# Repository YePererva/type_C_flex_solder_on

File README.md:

# Type C upgrade kits

Status: Work in progress

Stage: Search for affordable prototyping facility

## About:

This repository contains developments on **_in-situ_** upgrade kits for older Micro/Mini USB ports with USB Type C. The idea is to have flex-PCB (or on very thin FR-4), where:

- USB Type port is located on top layer, accompanied by a pair of 5K1 resistors. 
- Mirrored footprint of a Micro (or Mini) USB port is situated at the bottom layer.
- Use of 0603 size of resistors would keep this project manually solderable

Theoretically, it allows for upgrading older devices by directly soldering of adapter over existing footprint. 

The Content Repository contains three variations of adapters:

- `micro_edge`
    
    prototype of micro USB replacement, where alignment is done on the PCB edge, as is typical for ports.

- `mini_edge`
    
    prototype of mini USB replacement, where alignment is done on the PCB edge, as is typical for ports. It is interesting to note that the mini USB port appears to be of a greater length than that of the type C port.

- `micro_pads`
    
    this prototype is a design for a micro USB replacement, in which is allinged relatively to the pads of micro USB port. This is applicable in instances where the presence of additional circuitry in close proximity to the port renders edge alignment unfeasible. It results in a longer outlet of the Type C port protruding from the PCB edge.  

## Some visuals

|   | Micro Edge | Mini Edge | Micro Pads |
| ------------- | ------------- |  ------------- |  ------------- |
| Top View  |   |   |   |
| Bottom View  |   |   |   |

## Remarks / Thoughts / Things to test

- The utilisation of tape adhesive might be necessary for the positioning.
- Thin FR-4 might provide more rigidity than FlexPCBs
- Silkscreen has multiple perimeters. THis is for manual adjusting of form where space limitation might require it.
- For panelization of multiple designs, I found [this](https://github.com/buganini/Kikakuka) tool useful.

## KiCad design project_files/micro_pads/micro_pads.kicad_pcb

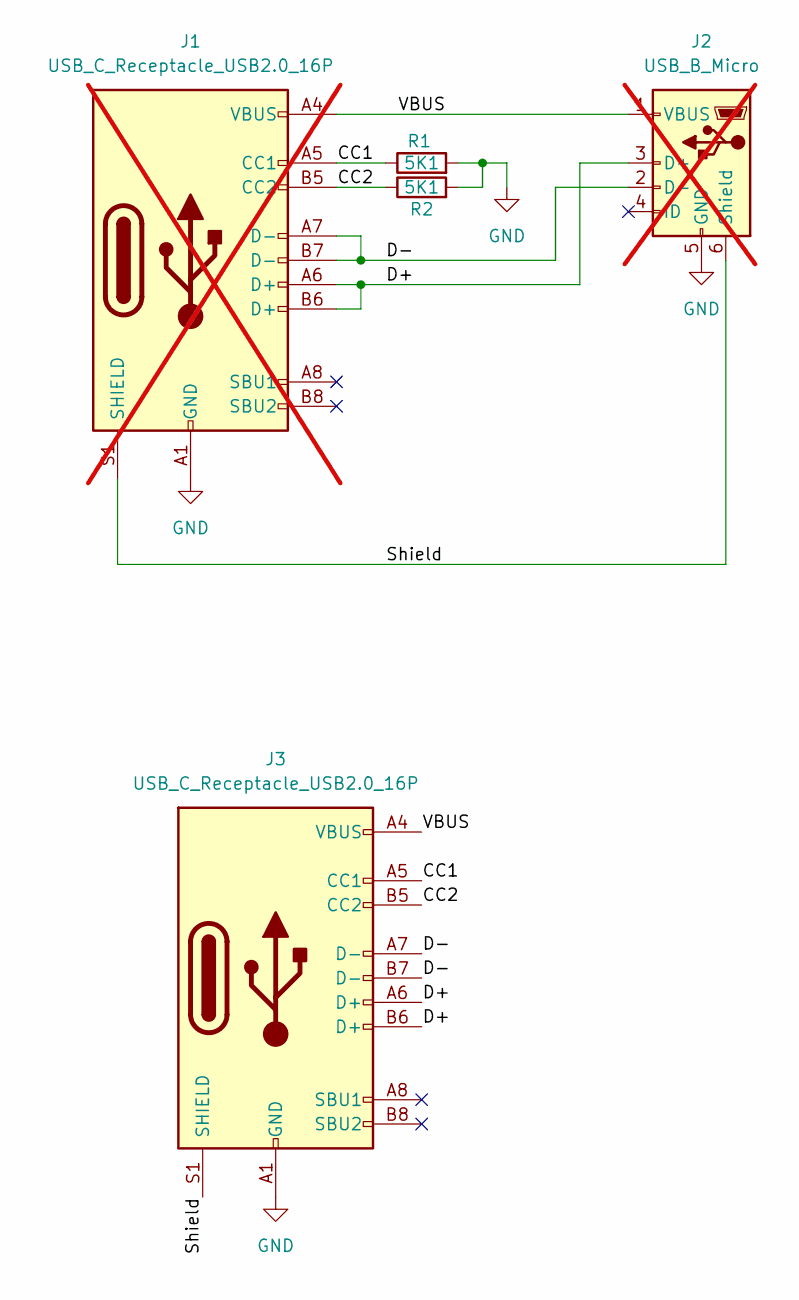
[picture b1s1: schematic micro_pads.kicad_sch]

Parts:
J1: USB_C_Receptacle_USB2.0_16P; USB_C_Receptacle_GCT_USB4110; not fitted
J2: USB_B_Micro; USB_Micro-B_Amphenol_10118194-0001LF_Horizontal; not fitted
J3: USB_C_Receptacle_USB2.0_16P; USB_C_Receptacle_GCT_USB4105-xx-A_16P_TopMnt_Horizontal
R1, R2: 5K1; R_0603_1608Metric

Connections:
/CC1: J1.A5 (CC1), J3.A5 (CC1), R1.1
/CC2: J1.B5 (CC2), J3.B5 (CC2), R2.1
/D+: J1.A6 (D+), J1.B6 (D+), J2.3 (D+), J3.A6 (D+), J3.B6 (D+)
/D-: J1.A7 (D-), J1.B7 (D-), J2.2 (D-), J3.A7 (D-), J3.B7 (D-)
/Shield: J1.S1 (SHIELD), J2.6 (Shield), J3.S1 (SHIELD)
/VBUS: J1.A4 (VBUS), J1.A9 (VBUS), J1.B4 (VBUS), J1.B9 (VBUS), J2.1 (VBUS), J3.A4 (VBUS), J3.A9 (VBUS), J3.B4 (VBUS), J3.B9 (VBUS)
GND: J1.A1 (GND), J1.A12 (GND), J1.B1 (GND), J1.B12 (GND), J2.5 (GND), J3.A1 (GND), J3.A12 (GND), J3.B1 (GND), J3.B12 (GND), R1.2, R2.2

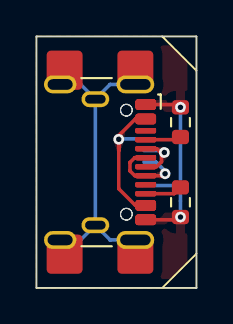
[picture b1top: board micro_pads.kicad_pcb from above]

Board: 2 copper layers, 8.9 x 14.0 mm, 5 parts (1 on the bottom side), 7 nets.

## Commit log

2025-04-22 first sync
    Gathering all prototypes in one place
2025-04-22 added panelizing config
